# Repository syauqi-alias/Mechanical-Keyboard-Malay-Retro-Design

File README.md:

# Mechanical-Keyboard-Malay-Retro-Design
A custom expose design through hole component Mechanical Keyboard with a bit of Malays art instill in it.

The schematic is open-source but the design is not.

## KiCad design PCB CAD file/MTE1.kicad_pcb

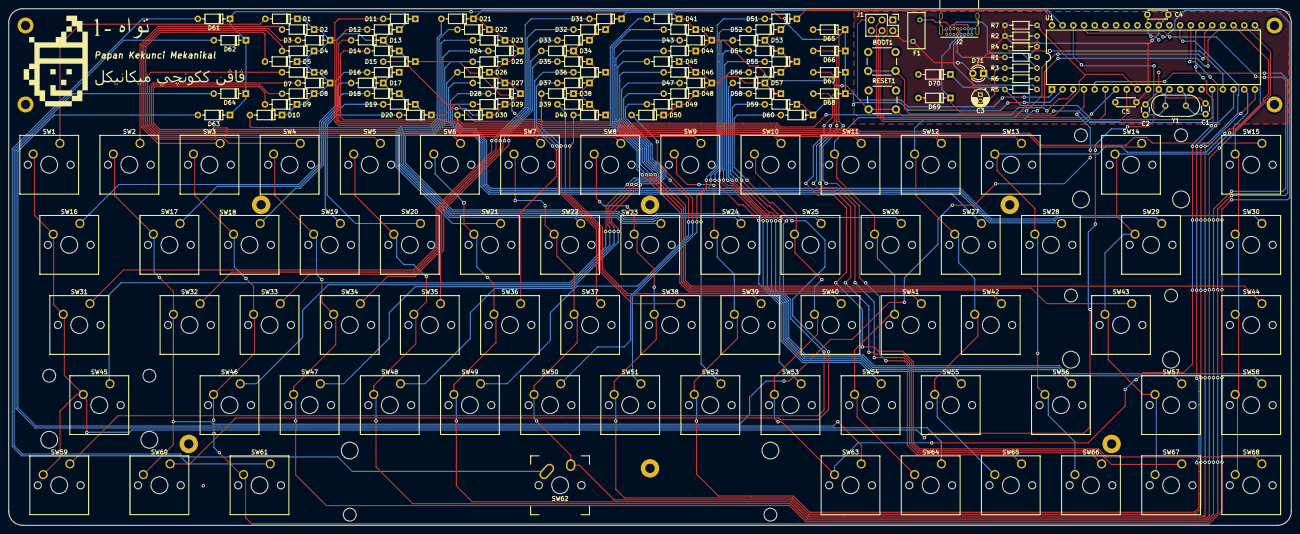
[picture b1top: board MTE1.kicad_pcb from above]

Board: 2 copper layers, 304.9 x 122.8 mm, 158 parts (0 on the bottom side), 105 nets.

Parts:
BOOT1: B1; SW_PUSH_6mm
C1, C2: C; C_Disc_D3.0mm_W1.6mm_P2.50mm
C3: CP1_Small; CP_Radial_D4.0mm_P1.50mm
C4, C5: C; C_Disc_D4.3mm_W1.9mm_P5.00mm
D1, D2, D3, D4, D5, D6, D7, D8, D9, D10, D11, D12, D13, D14, D15, D16, D17, D18, D19, D20, D21, D22, D23, D24, D25, D26, D27, D28, D29, D30, D31, D32, D33, D34, D35, D36, D37, D38, D39, D40, D41, D42, D43, D44, D45, D46, D47, D48, D49, D50, D51, D52, D53, D54, D55, D56, D57, D58, D59, D60, D61, D62, D63, D64, D65, D66, D67, D68: D; D_DO-35_SOD27_P7.62mm_Horizontal
D69, D70: 3.6V; D_DO-35_SOD27_P7.62mm_Horizontal
D71: LED; LED_D3.0mm
F1: Polyfuse_Small; Fuse_BelFuse_0ZRE0005FF_L8.3mm_W3.8mm
J1: AVR-ISP-6; PinHeader_2x03_P2.54mm_Vertical
J2: USB_C_Receptacle; USB_C_Receptacle_GCT_USB4085
R1, R3: 5.1k; R_Axial_DIN0204_L3.6mm_D1.6mm_P7.62mm_Horizontal
R2: 1.5k; R_Axial_DIN0204_L3.6mm_D1.6mm_P7.62mm_Horizontal
R4, R5, R6: 75R; R_Axial_DIN0204_L3.6mm_D1.6mm_P7.62mm_Horizontal
R7: 10k; R_Axial_DIN0204_L3.6mm_D1.6mm_P7.62mm_Horizontal
RESET1: B2; SW_PUSH_6mm
SW1, SW2, SW3, SW4, SW5, SW6, SW7, SW8, SW9, SW10, SW11, SW12, SW13, SW15, SW17, SW18, SW19, SW20, SW21, SW22, SW23, SW24, SW25, SW26, SW27, SW28, SW30, SW32, SW33, SW34, SW35, SW36, SW37, SW38, SW39, SW40, SW41, SW42, SW44, SW46, SW47, SW48, SW49, SW50, SW51, SW52, SW53, SW54, SW55, SW57, SW58, SW63, SW64, SW65, SW66, SW67, SW68: SW_SPST; SW_Cherry_MX_1.00u_PCB
SW14: SW_SPST; SW_Cherry_MX_2.00u_PCB
SW16, SW29: SW_SPST; SW_Cherry_MX_1.50u_PCB
SW31, SW56: SW_SPST; SW_Cherry_MX_1.75u_PCB
SW43, SW45: SW_SPST; SW_Cherry_MX_2.25u_PCB
SW59, SW60, SW61: SW_SPST; SW_Cherry_MX_1.25u_PCB
SW62: SW_SPST; MX-6.25U-ReversedStabilizers-NoLED
U1: ATmega32A-PU; DIP-40_W15.24mm
Y1: Crystal; Crystal_HC49-4H_Vertical

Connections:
+5V: C3.1, C4.1, C5.1, D71.2, F1.1, J1.2, R2.1, R7.1, U1.10, U1.30
D+: D70.1, R5.1, U1.16
D-: R4.1, U1.17
GND: BOOT1.1, C1.2, C2.2, C3.2, C4.2, C5.2, D69.2, D70.2, J1.6, J2.A1, J2.A12, J2.B1, J2.B12, J2.S1, R1.2, R3.1, R6.1, RESET1.1, U1.11, U1.31
MISO: J1.1, U1.7
MOSI: J1.4, U1.6
unnamed: C1.1, U1.13, Y1.1
unnamed: C2.1, U1.12, Y1.2
unnamed: D1.2, SW1.1
unnamed: D2.2, SW2.1
unnamed: D3.2, SW3.1
unnamed: D4.2, SW4.1
unnamed: D5.2, SW5.1
unnamed: D6.2, SW6.1
unnamed: D7.2, SW7.1
unnamed: D8.2, SW8.1
unnamed: D9.2, SW9.1
unnamed: D10.2, SW10.1
unnamed: D11.2, SW11.1
unnamed: D12.2, SW12.1
unnamed: D13.2, SW13.1
unnamed: D14.2, SW14.1
unnamed: D15.2, SW15.1
unnamed: D16.2, SW16.1
unnamed: D17.2, SW17.1
unnamed: D18.2, SW18.1
unnamed: D19.2, SW19.1
unnamed: D20.2, SW20.1
unnamed: D21.2, SW21.1
unnamed: D22.2, SW22.1
unnamed: D23.2, SW23.1
unnamed: D24.2, SW24.1
unnamed: D25.2, SW25.1
unnamed: D26.2, SW26.1
unnamed: D27.2, SW27.1
unnamed: D28.2, SW28.1
unnamed: D29.2, SW29.1
unnamed: D30.2, SW30.1
unnamed: D31.2, SW31.1
unnamed: D32.2, SW32.1
unnamed: D33.2, SW33.1
unnamed: D34.2, SW34.1
unnamed: D35.2, SW35.1
unnamed: D36.2, SW36.1
unnamed: D37.2, SW37.1
unnamed: D38.2, SW38.1
unnamed: D39.2, SW39.1
unnamed: D40.2, SW40.1
unnamed: D41.2, SW41.1
unnamed: D42.2, SW42.1
unnamed: D43.2, SW43.1
unnamed: D44.2, SW44.1
unnamed: D45.2, SW45.1
unnamed: D46.2, SW46.1
unnamed: D47.2, SW47.1
unnamed: D48.2, SW48.1
unnamed: D49.2, SW49.1
unnamed: D50.2, SW50.1
unnamed: D51.2, SW51.1
unnamed: D52.2, SW52.1
unnamed: D53.2, SW53.1
unnamed: D54.2, SW54.1
unnamed: D55.2, SW55.1
unnamed: D56.2, SW56.1
unnamed: D57.2, SW57.1
unnamed: D58.2, SW58.1
unnamed: D59.2, SW59.1
unnamed: D60.2, SW60.1
unnamed: D61.2, SW61.1
unnamed: D62.2, SW62.1
unnamed: D63.2, SW63.1
unnamed: D64.2, SW64.1
unnamed: D65.2, SW65.1
unnamed: D66.2, SW66.1
unnamed: D67.2, SW67.1
unnamed: D68.2, SW68.1
unnamed: D69.1, J2.A7, J2.B7, R2.2, R4.2
unnamed: D71.1, R6.2
unnamed: J2.A5, R1.1
unnamed: J2.A6, J2.B6, R5.2
unnamed: J2.B5, R3.2
SCK: J1.3, U1.8
VCC: F1.2, J2.A4, J2.A9, J2.B4, J2.B9
boot: BOOT1.2, U1.18
col0: SW1.2, SW16.2, SW31.2, SW45.2, SW59.2, U1.38
col1: SW2.2, SW17.2, SW32.2, SW60.2, U1.4
col2: SW3.2, SW18.2, SW33.2, SW46.2, SW61.2, U1.37
col3: SW4.2, SW19.2, SW34.2, SW47.2, U1.5
col4: SW5.2, SW20.2, SW35.2, SW48.2, U1.36
col5: SW6.2, SW21.2, SW36.2, SW49.2, U1.19
col6: SW7.2, SW22.2, SW37.2, SW50.2, SW62.2, U1.20
col7: SW8.2, SW23.2, SW38.2, SW51.2, U1.28
col8: SW9.2, SW24.2, SW39.2, SW52.2, U1.27
col9: SW10.2, SW25.2, SW40.2, SW53.2, SW63.2, U1.26
col10: SW11.2, SW26.2, SW41.2, SW54.2, SW64.2, U1.25
col11: SW12.2, SW27.2, SW42.2, SW55.2, SW65.2, U1.24
col12: SW13.2, SW28.2, SW56.2, SW66.2, U1.23
col13: SW14.2, SW29.2, SW43.2, SW57.2, SW67.2, U1.22
col14: SW15.2, SW30.2, SW44.2, SW58.2, SW68.2, U1.21
reset: J1.5, R7.2, RESET1.2, U1.9
row0: D1.1, D2.1, D3.1, D4.1, D5.1, D6.1, D7.1, D8.1, D9.1, D10.1, D11.1, D12.1, D13.1, D14.1, D15.1, U1.3
row1: D16.1, D17.1, D18.1, D19.1, D20.1, D21.1, D22.1, D23.1, D24.1, D25.1, D26.1, D27.1, D28.1, D29.1, D30.1, U1.39
row2: D31.1, D32.1, D33.1, D34.1, D35.1, D36.1, D37.1, D38.1, D39.1, D40.1, D41.1, D42.1, D43.1, D44.1, U1.2
row3: D45.1, D46.1, D47.1, D48.1, D49.1, D50.1, D51.1, D52.1, D53.1, D54.1, D55.1, D56.1, D57.1, D58.1, U1.40
row4: D59.1, D60.1, D61.1, D62.1, D63.1, D64.1, D65.1, D66.1, D67.1, D68.1, U1.1

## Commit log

2022-09-16 Create PCB CAD file
2022-09-16 foo.txt
    Initial file
2022-09-16 Keyboard overlook
2022-09-16 Add files via upload
    This is the part needed for if you ever wanted to build your own, all through hole component.
